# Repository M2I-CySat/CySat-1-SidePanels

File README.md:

# CySat-SidePanels
The side panel hardware designs for the satellite

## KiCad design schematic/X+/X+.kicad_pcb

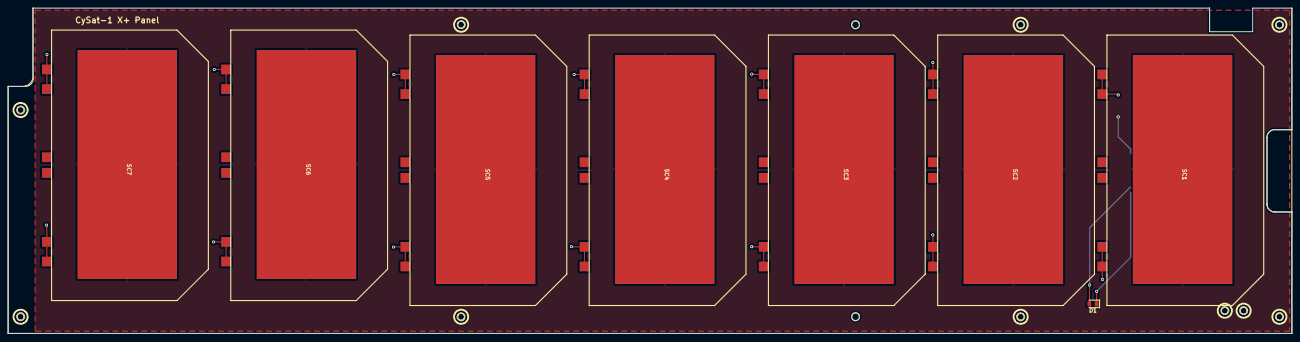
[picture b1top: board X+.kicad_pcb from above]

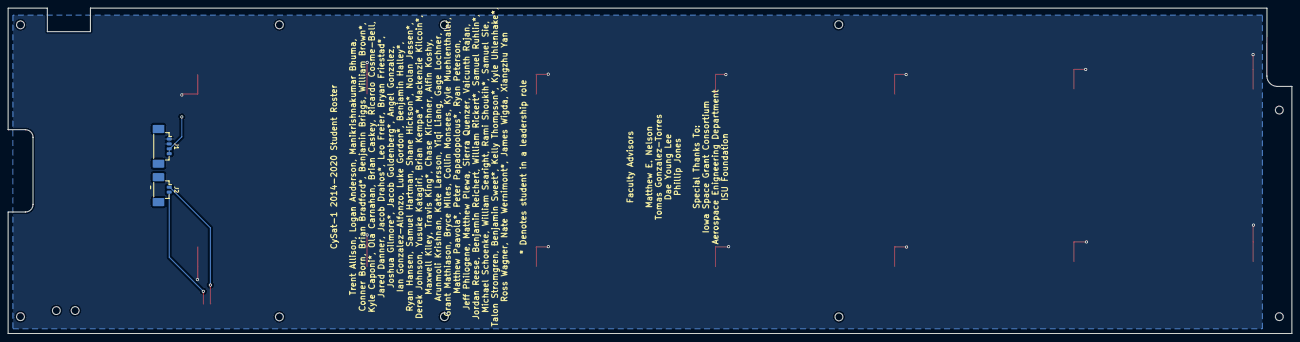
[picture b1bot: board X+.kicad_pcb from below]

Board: 2 copper layers, 327.5 x 83.0 mm, 10 parts (2 on the bottom side), 4 nets.

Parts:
D1: D_Photo; D_0805_2012Metric
J1: Conn_01x04; Molex_PicoBlade_53398-0471_1x04-1MP_P1.25mm_Vertical
J2: Conn_01x02; Molex_PicoBlade_53398-0271_1x02-1MP_P1.25mm_Vertical
SC1, SC2, SC3, SC4, SC5, SC6, SC7: Solar_Cell; Spectrolabs_UTJ

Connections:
unnamed: D1.1 (K), J2.2
unnamed: D1.2 (A), J2.1
VCC: J1.3, J1.4, SC1.1 (+), SC2.1 (+), SC3.1 (+), SC4.1 (+), SC5.1 (+), SC6.1 (+), SC7.1 (+)
VSS: J1.1, J1.2, SC1.2 (-), SC2.2 (-), SC3.2 (-), SC4.2 (-), SC5.2 (-), SC6.2 (-), SC7.2 (-)

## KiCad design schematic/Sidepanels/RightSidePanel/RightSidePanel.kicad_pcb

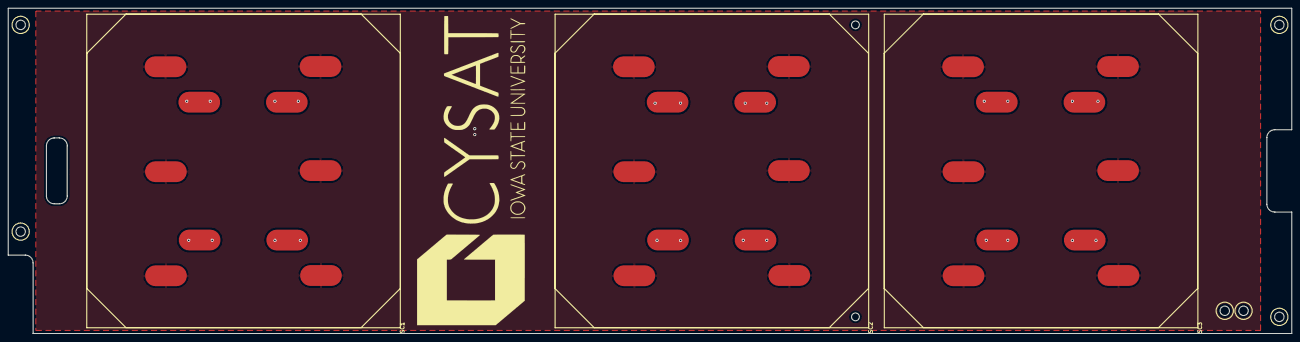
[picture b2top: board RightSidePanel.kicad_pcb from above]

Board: 2 copper layers, 327.5 x 83.0 mm, 4 parts (1 on the bottom side), 2 nets, no tracks yet.

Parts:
J1: Conn_01x04; Molex_PicoBlade_53398-0471_04x1.25mm_Straight
SC1, SC2, SC3: Solar_Cell; ISS_SolarCell

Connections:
VCC: J1.3, J1.4, SC1.1, SC2.1, SC3.1
VSS: J1.1, J1.2, SC1.2, SC2.2, SC3.2

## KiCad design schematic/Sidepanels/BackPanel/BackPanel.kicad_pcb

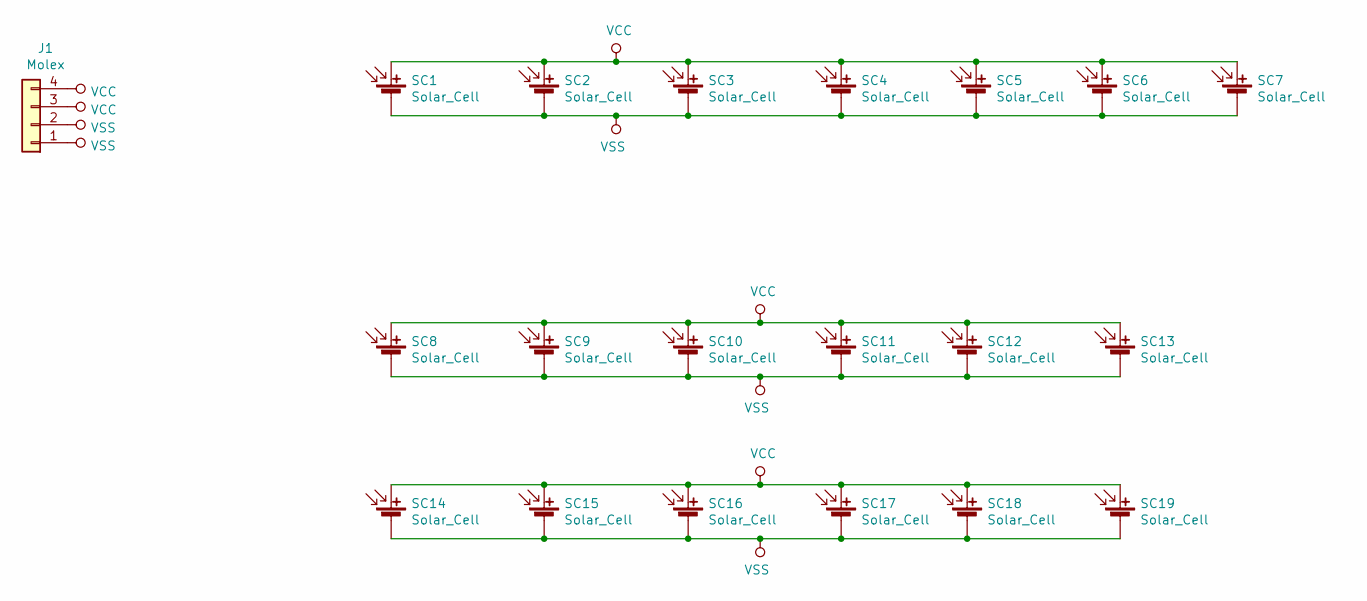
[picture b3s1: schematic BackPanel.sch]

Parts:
J1: Molex; Molex_PicoBlade_53398-0471_04x1.25mm_Straight
SC1, SC2, SC3, SC4, SC5, SC6, SC7: Solar_Cell; Spectrolab
SC8, SC9, SC10, SC11, SC12, SC13, SC14, SC15, SC16, SC17, SC18, SC19: Solar_Cell; TriSelectSolarPanel

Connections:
VCC: J1.3, J1.4, SC1.1 (+), SC2.1 (+), SC3.1 (+), SC4.1 (+), SC5.1 (+), SC6.1 (+), SC7.1 (+), SC8.1 (+), SC9.1 (+), SC10.1 (+), SC11.1 (+), SC12.1 (+), SC13.1 (+), SC14.1 (+), SC15.1 (+), SC16.1 (+), SC17.1 (+), SC18.1 (+), SC19.1 (+)
VSS: J1.1, J1.2, SC1.2 (-), SC2.2 (-), SC3.2 (-), SC4.2 (-), SC5.2 (-), SC6.2 (-), SC7.2 (-), SC8.2 (-), SC9.2 (-), SC10.2 (-), SC11.2 (-), SC12.2 (-), SC13.2 (-), SC14.2 (-), SC15.2 (-), SC16.2 (-), SC17.2 (-), SC18.2 (-), SC19.2 (-)

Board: 2 copper layers, 20 parts (1 on the bottom side), 2 nets, no tracks yet.

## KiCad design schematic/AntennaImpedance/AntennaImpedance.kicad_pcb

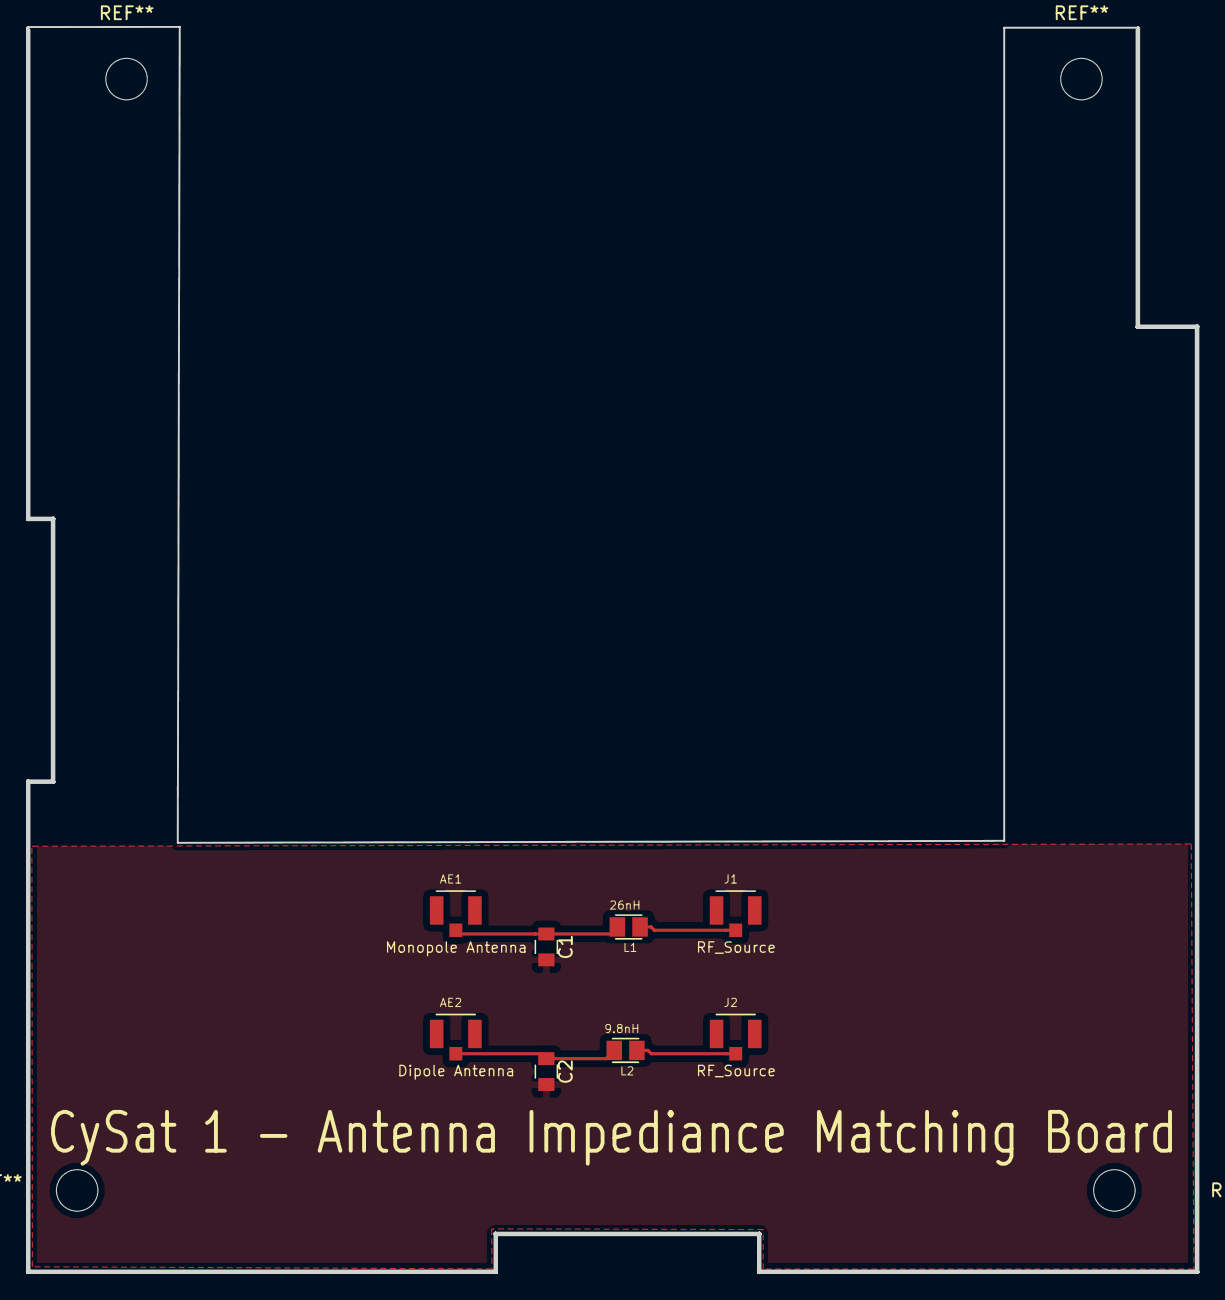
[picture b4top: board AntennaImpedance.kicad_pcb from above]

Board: 2 copper layers, 90.3 x 96.1 mm, 8 parts (0 on the bottom side), 5 nets.

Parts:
AE1: Monopole Antenna; TE_1909763-1
AE2: Dipole Antenna; TE_1909763-1
C1, C2: 1pF; C_0805
J1, J2: RF_Source; TE_1909763-1
L1: 26nH; INDC2012X125
L2: 9.8nH; INDC2012X125

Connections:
GND: C1.2, C2.2
unnamed: AE1.1, C1.1, L1.2
unnamed: AE2.1, C2.1, L2.2
unnamed: J1.1, L1.1
unnamed: J2.1, L2.1

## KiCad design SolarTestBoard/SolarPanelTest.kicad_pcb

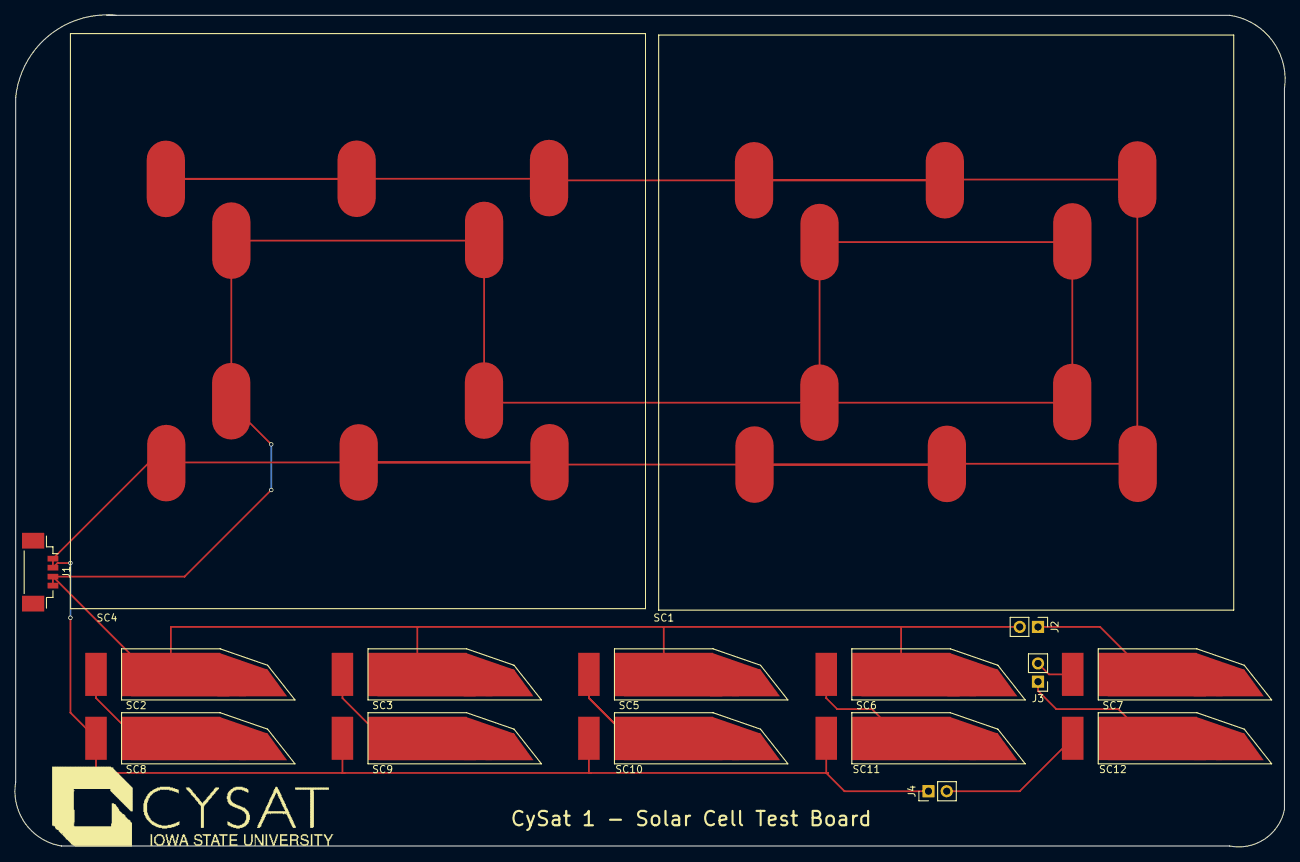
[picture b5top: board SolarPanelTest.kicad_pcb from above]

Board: 2 copper layers, 176.7 x 115.8 mm, 17 parts (0 on the bottom side), 10 nets.

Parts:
J1: Conn_01x04; Molex_PicoBlade_53398-0471_04x1.25mm_Straight
J2, J4: Two Cells; Pin_Header_Straight_1x02_Pitch2.54mm
J3: Split Cells; Pin_Header_Straight_1x02_Pitch2.54mm
LOGO: LOGO
SC1, SC4: Solar_Cell; ISS_SolarCell
SC2, SC3, SC5, SC6, SC7, SC8, SC9, SC10, SC11, SC12: Solar_Cell; TriSelectSolarPanel

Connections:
A: J1.3, J1.4, J2.2, SC1.1, SC2.1, SC3.1, SC4.1, SC5.1, SC6.1
B: J2.1, SC7.1
C: J3.2, SC7.2
D: J3.1, SC12.1
E: J4.2, SC12.2
F: J1.1, J1.2, J4.1, SC1.2, SC4.2, SC8.2, SC9.2, SC10.2, SC11.2
unnamed: SC2.2, SC8.1
unnamed: SC3.2, SC9.1
unnamed: SC5.2, SC10.1
unnamed: SC6.2, SC11.1

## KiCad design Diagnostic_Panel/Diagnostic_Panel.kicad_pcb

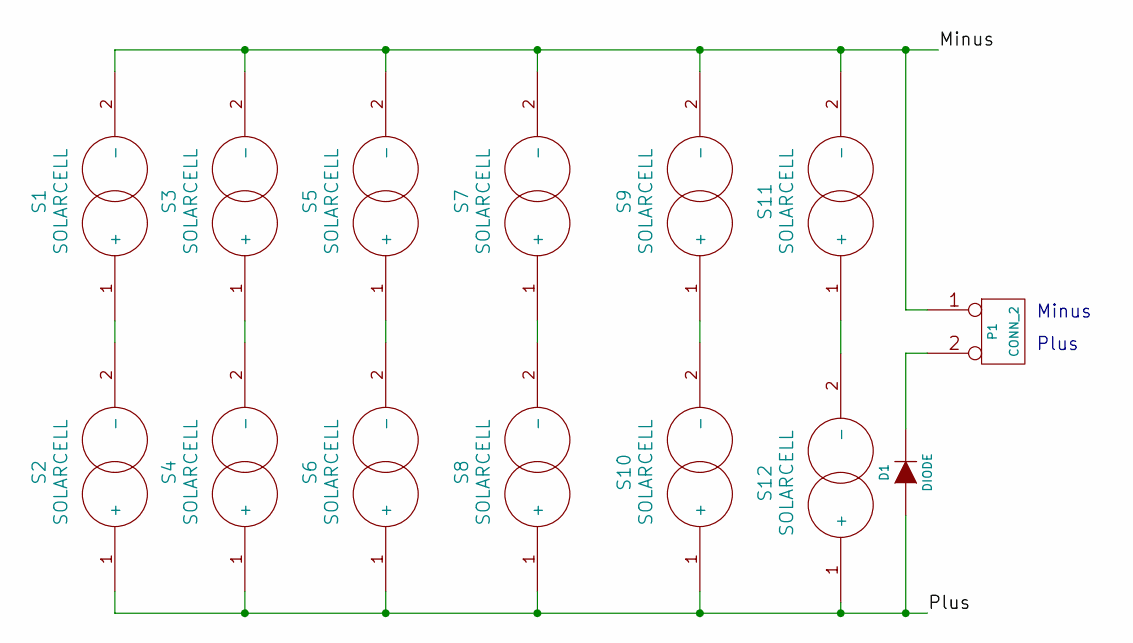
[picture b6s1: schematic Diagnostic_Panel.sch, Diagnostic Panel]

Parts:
D1: DIODE
P1: CONN_2
S1, S2, S3, S4, S5, S6, S7, S8, S9, S10, S11, S12: SOLARCELL

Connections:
/Minus: P1.1, S1.2 (-), S3.2 (-), S5.2 (-), S7.2 (-), S9.2 (-), S11.2 (-)
/Plus: D1.1 (A), S2.1 (+), S4.1 (+), S6.1 (+), S8.1 (+), S10.1 (+), S12.1 (+)
unnamed: S1.1 (+), S2.2 (-)
unnamed: S11.1 (+), S12.2 (-)
unnamed: D1.2 (K), P1.2 (PM)
unnamed: S7.1 (+), S8.2 (-)
unnamed: S9.1 (+), S10.2 (-)
unnamed: S5.1 (+), S6.2 (-)
unnamed: S3.1 (+), S4.2 (-)

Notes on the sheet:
Plus
Minus

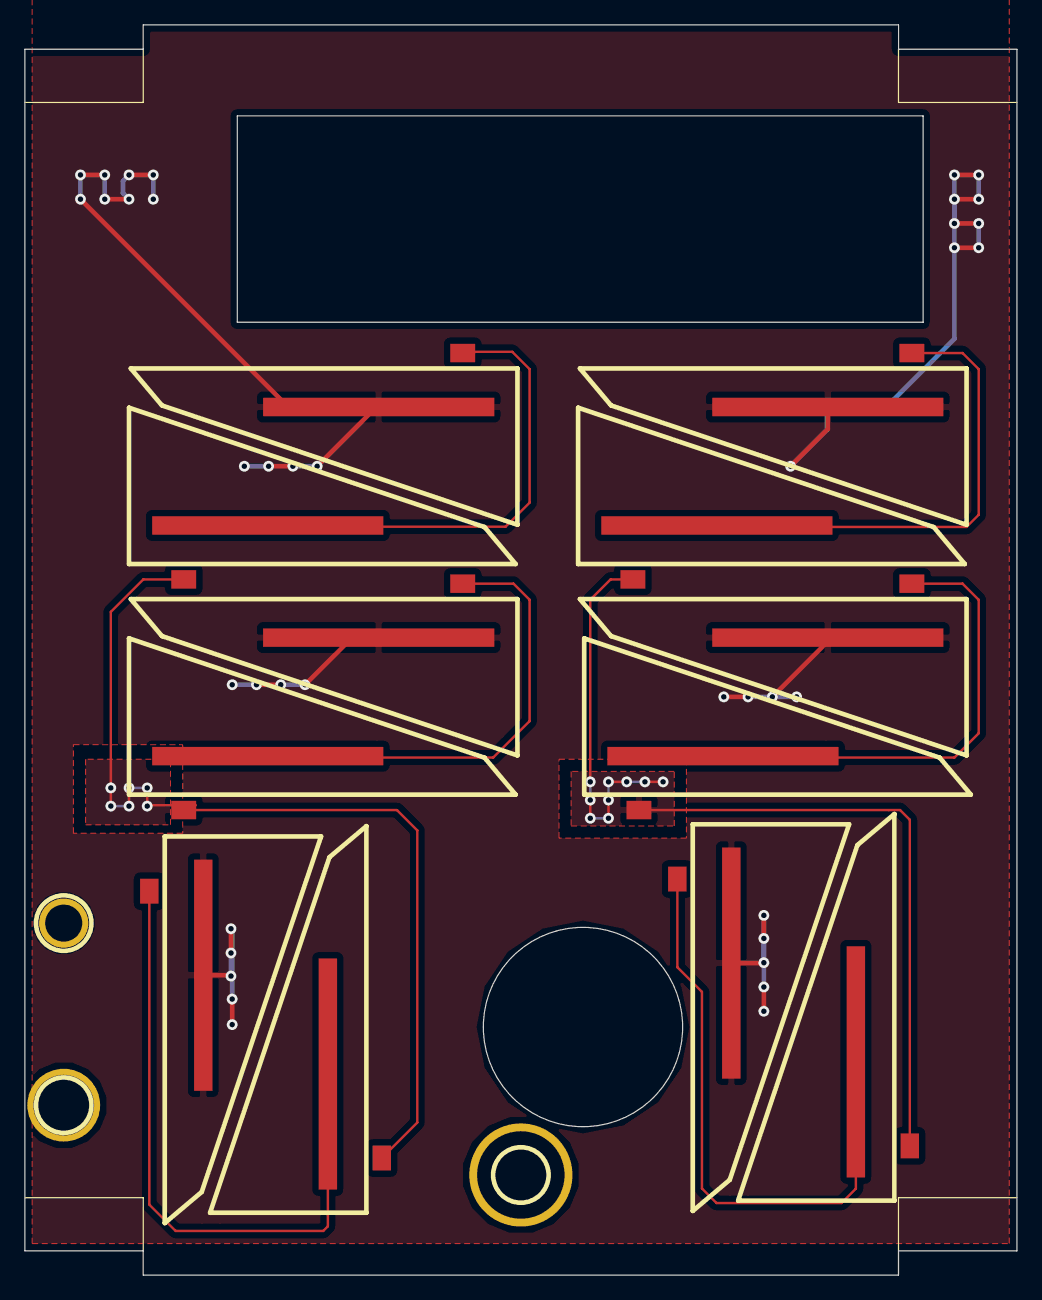
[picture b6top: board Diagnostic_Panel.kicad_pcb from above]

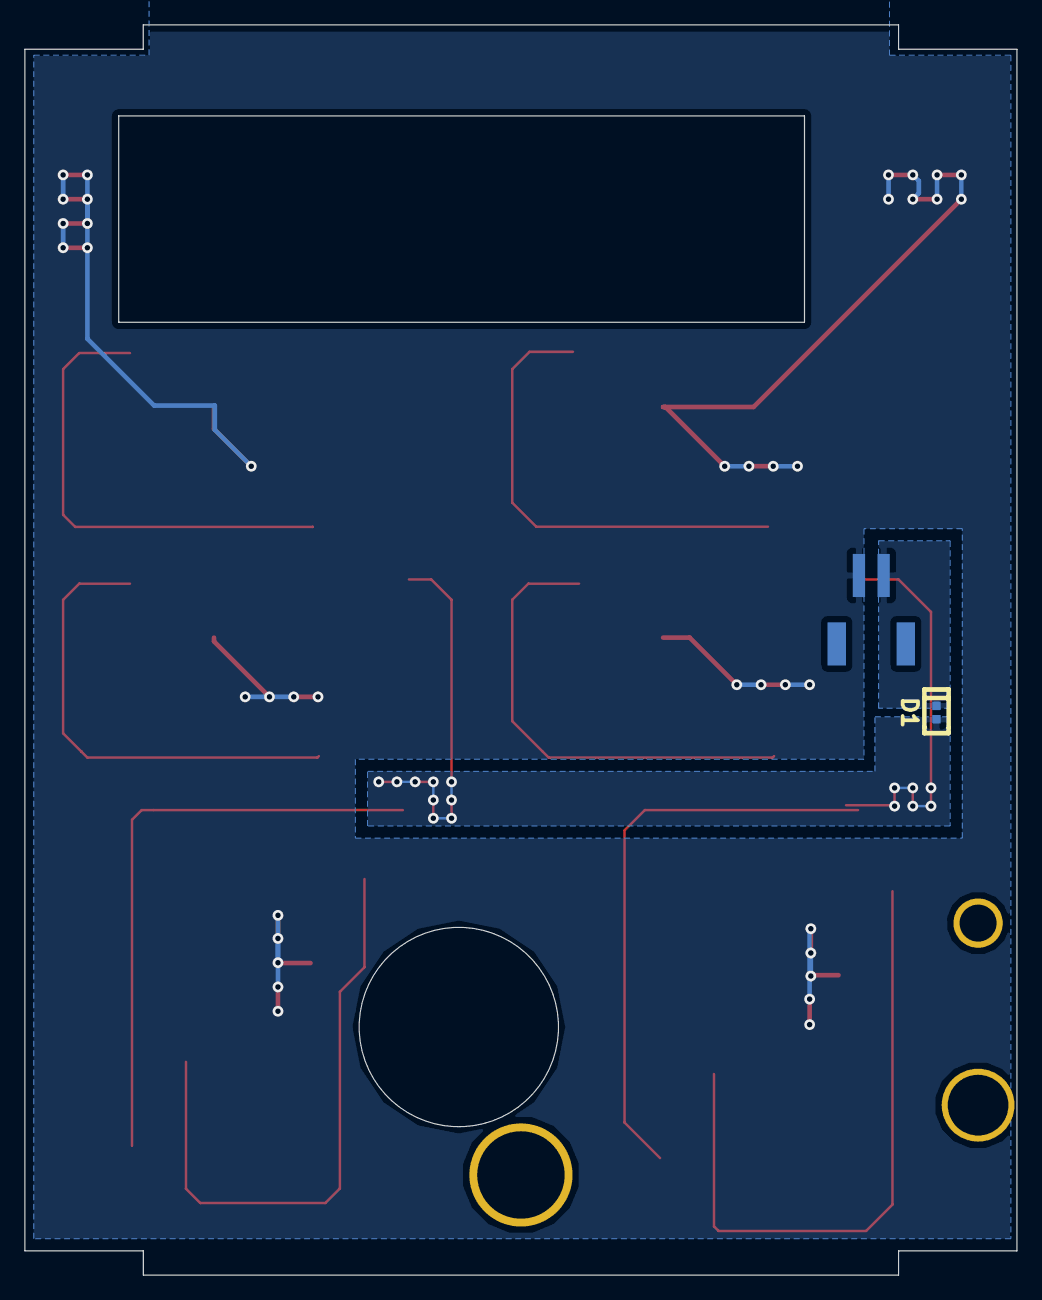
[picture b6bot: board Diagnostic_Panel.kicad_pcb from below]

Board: 2 copper layers, 81.7 x 103.0 mm, 17 parts (2 on the bottom side), 9 nets.

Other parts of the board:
1PIN, 1PIN#2, 1PIN#3: P***; 1pin

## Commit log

2015-04-04 Top and Diagnostic Port Panel Designs
2015-04-15 Added git ignore file
2015-04-15 Added camera hole to side panels
2015-04-15 Added revision text
2015-04-15 Created new gerber files
2018-06-19 Solar Cell Data Sheets
2018-06-29 Completed Solar Cell test board
2018-07-03 Changed footprints to add troubleshooting jumpers and the molex connector
2018-07-03 Finished v1
2018-07-20 Fixed gerber file
2018-07-29 Fixed gerber
2018-07-31 Cleaning up
2018-07-31 Added Impediance matching board
2018-09-12 Created resistor bracket
2018-09-12 Cleaning up directory structure
2018-09-13 Updated gerber
2018-09-13 Shifted things about
2018-09-15 Added to the silkscreen
2018-09-15 Silkscreen
2018-09-18 Staring side panel pcbs
2019-01-09 Finished Right, Back 90% done.
2019-01-19 FINALLY got the pcb art I wanted
2019-04-11 Add files via upload
    All solar panels PCBs made up to the date of 4_11_2019
2019-07-03 Minor fix
2019-07-13 Create Description
2019-07-13 Added X- Files
2019-07-13 Added Y+ Files
2019-07-13 Added Y- files
2019-07-13 Added Z- Files
2019-07-19 Minor updates
2019-09-27 Flipped and added TrisolX cells
2019-09-27 Flipped and/or added TrisolX cells
2019-10-02 Flipped/removed Trisol Cells
2019-10-02 Fixed Trisol Cells
2019-10-02 Fixed TrisolX Cells
2019-10-05 Adding Gerber Files via zipped folder
2020-01-10 Removed older zip file
2020-07-08 First attempt at modifying to all Spectrolabs. NOT COMPLETE
2020-07-19 Updated X-
    Updated X-, added 3D model, layout complete. ERC and DRC pass
2020-07-21 Update to X panels
    Routing completed on both, solar panel change out complete on X+. Re-did library and page settings. DRC checks out.
2020-07-22 Completed y-
2020-07-22 Update to Y+
2020-07-24 Update to all boards
    Added labels to boards to resolve issue #2
    Added names of students and faculty to boards
    Generated Step files to resolve issue #4, please note the export does include the silkscreen.
2021-03-05 Added cutout to y+
    Generated Gerber files
2021-03-05 Added cutout to X+ board
    Generated Gerber files
2021-03-05 updated on save
2021-03-05 Added cutout
    Generated Gerber files
2022-04-22 Logo
2022-05-18 Start on board changes
2022-06-30 Push of all changes made for June update
    Major change was in the solar cell and creating a new library based on the old one.
2022-06-30 Massive file clean up
    Major clean up of a number of old files and things that are not relevant. All of these will still be in past commits.
2022-11-04 Gerber files
2023-08-01 Update for KiCad
